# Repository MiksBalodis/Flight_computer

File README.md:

# Aktīvās kontroles raķetes avionikas sistēma

## Projekta apraksts
Šis projekts paredz aktīvās kontroles raķetes avionikas sistēmas izstrādi, kas ietver gan raķetē iebūvētu avionikas datoru, gan zemes bāzi datu saņemšanai, uzglabāšanai un analīzei. Sistēma nodrošina aktīvu trajektorijas korekciju reāllaikā, izmantojot sensoru datus, vadības algoritmus un elektroniskos izpildmehānismus.

Projektā tiek apvienotas iegultās sistēmas, signālu apstrāde, vadības algoritmi, telemetrija un lietotāja saskarnes izstrāde.

**Projektu izstrādā:**  
Aleksandrs Jesiļevskis  
Miks Balodis  

---

## Projekta mērķis
Izstrādāt:
- raķetes avionikas datoru ar aktīvas trajektorijas korekcijas iespējām,
- zemes bāzi lidojuma datu saņemšanai un analīzei,
- drošu un papildināmu sistēmu, kas piemērota eksperimentālām lieljaudas raķetēm.

Sistēmai jāspēj:
- reāllaikā noteikt raķetes stāvokli,
- veikt aktīvo vadību ar vairākām kontroles spurām,
- ierakstīt un uzglabāt lidojuma datus,
- nodrošināt saziņu ar zemes bāzi lidojuma laikā.

---

## Idejas rašanās
Ideja radās, balstoties uz **RTU Lieljaudas raķeškomandas (RTU HPR)** 2025. gada 1. semestra projektu – aktīvās rotācijas kontroles raķeti. Šī projekta ietvaros tika izmantots RP2040 mikrokontrolieris, kuram konstatēti vairāki ierobežojumi:
- nav iebūvēta peldošā komata vienības (FPU),
- ierobežota programmas atmiņa,
- augsts enerģijas patēriņš.

Lai šos trūkumus novērstu, projektā tiek izvēlēts **STM32F405RGT6**, kas nodrošina augstāku veiktspēju, FPU atbalstu un DSP instrukcijas.

---

## Idejas apraksts

### Projekta lietotāji
- studentu raķešu komandas,
- augstskolu/vidusskolu eksperimentēšanas grupas,
- iegulto sistēmu un vadības algoritmu izstrādātāji,
- eksperimentālu raķešu un bezpilota sistēmu entuziasti.

### Izmantotās tehnoloģijas
- **Iegultās sistēmas:** STM32 (ARM Cortex-M4)
- **Sensori:** barometrs, IMU, GNSS
- **Vadības algoritmi:** PID, Kalmana filtrs
- **Telemetrija:** sub-GHz radio sakari
- **Programmatūra:** C/C++, MatLab/Simulink (simulācijas), JavaScript un Svelte (GUI)
- **Projektēšana:** KiCad

### Piegādes formāts
Projekta rezultāts būs:
- raķetes avionikas sistēmas plate (PCB),
- iegultā programmatūra gatava demonstratīvam raķetes lidojumam (firmware),
- zemes bāzes programmatūra (GUI),
- dokumentācija.

Šāda pieeja ļauj sistēmu izmantot gan eksperimentālos lidojumos, gan simulācijās.

---

## Aktīvā kontrole
Aktīvā kontrole ir vadības sistēma, kas lidojuma laikā nepārtraukti:
- mēra raķetes stāvokli (leņķi, ātrumu, rotāciju),
- aprēķina nepieciešamos labojumus,
- ģenerē PWM signālus izpildmehānismiem servo kontrolētām spurām.

Sistēma atbalsta līdz **4 aktīvām spurām**, katrai paredzot atsevišķu PWM kanālu. Salīdzinājumā ar pasīvo kontroli, aktīvā kontrole spēj reaģēt uz ārējiem traucējumiem un uzlabot stabilitāti un precizitāti.

---

## Risinājuma arhitektūra

### Konceptuālais modelis
Sistēma sastāv no trim galvenajiem blokiem:
1. **Sensoru slānis** – datu iegūšana
2. **Vadības un apstrādes slānis** – aprēķini un lēmumu pieņemšana
3. **Izpildes un komunikācijas slānis** – kontrole, datu uzglabāšana un pārraide

### Tehniskā arhitektūra

#### MCU
- **STM32F405RGT6** - mikrokontrolieris datu apstrādei un komandu nodošanai

#### Sensori
- **BMP388** – barometrs augstuma noteikšanai
- **LSM6DSO** – IMU (akselerometrs + žiroskops)
- **MAX-M10S** – GNSS modulis augstas precizitātes pozīcijai

#### Datu uzglabāšana
- **MXL1606** – lidojuma datu ierakstīšanai (USB Mass Storage režīms)
- **24LC64 EEPROM** – konfigurācijas datiem

#### Telemetrija
- **EBYTE E22-400M22S** - LoRa moudlis saziņai ar zemes bāzi (433 MHz)

#### Vadība
- PWM signāli spuru servo
- PID regulators
- Kalmana filtrs stāvokļa novērtēšanai

---
## Izstrādes plāns (10 nedēļas)

Projekta izstrāde ir plānota 10 nedēļu laikā, pieņemot, ka avionikas plate jau ir uzdizainēta un pasūtīta, un nākamais solis ir tās salodēšana. Darbs tiek sadalīts starp diviem izstrādātājiem, lai maksimāli efektīvi izmantotu paralēlu izstrādi.

### Lomu sadalījums
- **Aleksandrs** – iegultās sistēmas programmēšana, STM32 firmware, sensoru draiveri, datu plūsma, vadība un telemetrija, sistēmas arhitektūras lēmumi,  integrācija, testēšana un dokumentācija.
- **Miks** – raķetes tehniskā daļa, mehāniskā integrācija, Matlab/Simulink simulācijas, vadības algoritmu modelēšana un zemes stacijas aparatūra, sistēmas arhitektūras lēmumi,  integrācija, testēšana un dokumentācija.

---

### 1. nedēļa – Sistēmas inicializācija un modeļu sagatavošana
**Aleksandrs:**
- STM32CubeIDE projekta izveide
- Pulksteņu (clock tree) un pamata perifēriju konfigurācija
- Debug interfeisa (SWD/UART) inicializācija

**Miks:**
- Raķetes kustības konceptuālā modeļa izstrāde
- Aktīvās kontroles uzdevuma definēšana
- Sensoru mērījumu teorētisko modeļu izveide

**Rezultāts:**  
MCU veiksmīgi startē un sistēmas matemātiskais modelis ir definēts.

---

### 2. nedēļa – Perifēriju un datu plūsmas pamati
**Aleksandrs:**
- GPIO, UART, SPI un I2C konfigurācija
- DMA izmantošanas pamati datu pārsūtīšanai
- Vienkārša datu izvada testēšana

**Miks:**
- PID regulatora struktūras izveide Matlab/Simulink
- Sākotnējo vadības parametru novērtēšana
- Avionikas plates salodēšana

**Rezultāts:**  
MCU spēj komunicēt ar perifērijām, un PID struktūra ir gatava simulācijām, plate ir salodēta.

---

### 3. nedēļa – Avionikas plates salodēšana un sensoru testēšana
**Aleksandrs:**
- IMU (LSM6DSO) un barometra (BMP388) draiveru izstrāde
- Sensoru datu nolasīšana un izvadīšana caur UART

**Miks:**
- Barošanas un signālu līmeņu pārbaude
- Sensoru fiziskās integrācijas novērtēšana

**Rezultāts:**  
Pilnībā funkcionējoši aktīvie sensori.

---

### 4. nedēļa – GNSS un sensoru apvienošana
**Aleksandrs:**
- GNSS (MAX-M10S) draivera izstrāde
- Laika sinhronizācija starp sensoriem
- Datu struktūru definēšana

**Miks:**
- Sensoru kalibrācijas metodes
- Kļūdu modelēšana
- Mērījumu precizitātes izvērtēšana

**Rezultāts:**  
Apvienoti visi sensoru dati vienotā laika skalā.

---

### 5. nedēļa – Aktīvā vadība un izpildmehānismi
**Aleksandrs:**
- PWM izvades konfigurācija
- Taimeru konfigurācija izpildmehānismiem
- Izpildmehānismu testēšana

**Miks:**
- PID parametru regulēšana Simulink vidē
- Stabilitātes analīze
- Vadības algoritma validācija simulācijā

**Rezultāts:**  
Izpildmehānismi reaģē uz vadības signāliem paredzētajā veidā.

---

### 6. nedēļa – Datu apstrāde un uzglabāšana
**Aleksandrs:**
- USB Mass Storage režīma ieviešana
- Datu struktūras optimizācija

**Miks:**
- Kalmana filtra izstrāde Simulink vidē
- Algoritma sagatavošana ieviešanai C kodā

**Rezultāts:**  
Stabili ierakstīti un izgūstami lidojuma dati.

---

### 7. nedēļa – Telemetrija un zemes stacijas aparatūra
**Aleksandrs:**
- Telemetrijas protokola izstrāde
- EBYTE E22 radio moduļa integrācija
- Datu pakešu formāta definēšana

**Miks:**
- Zemes stacijas plates arhitektūras izstrāde
- Komponentu izvēle un shēmas dizains
- Komunikācijas interfeisa plānošana

**Rezultāts:**  
Bezvadu datu pārraide starp raķeti un zemes staciju.

---

### 8. nedēļa – Zemes stacijas programmatūra un GUI
**Aleksandrs:**
- Seriālās komunikācijas protokols ar datoru
- Telemetrijas datu parsēšana

**Miks:**
- Grafiskās lietotāja saskarnes izstrāde (Svelte)
- Reāllaika grafiki un datu attēlošana
- Datu eksportēšana analīzei

**Rezultāts:**  
Darbojoša zemes stacija ar reāllaika datu vizualizāciju.

---

### 9. nedēļa – Integrācija un sistēmas testi
**Aleksandrs:**
- Pilna vadības cikla integrācija
- Kļūdu apstrāde un drošības mehānismi

**Miks:**
- Vibrāciju testi
- Sensoru trokšņu ietekmes pārbaude

**Rezultāts:**  
Stabila un integrēta sistēma bez kritiskām kļūdām.

---

### 10. nedēļa – Stabilizācija un dokumentācija
**Abi:**
- Koda un aparatūras kļūdu labošana
- Projekta dokumentācijas pabeigšana
- Demonstrācijas sagatavošana

**Rezultāts:**  
Pilnībā sagatavots projekts demonstrācijai un prezentācijai.

---

## Projekta izstrādes grafiks

---

## Licence
Licence tiks noteikta projekta vēlākā izstrādes posmā.

---

## Kontakti
Jautājumu vai sadarbības gadījumā sazināties ar projekta izstrādātājiem.

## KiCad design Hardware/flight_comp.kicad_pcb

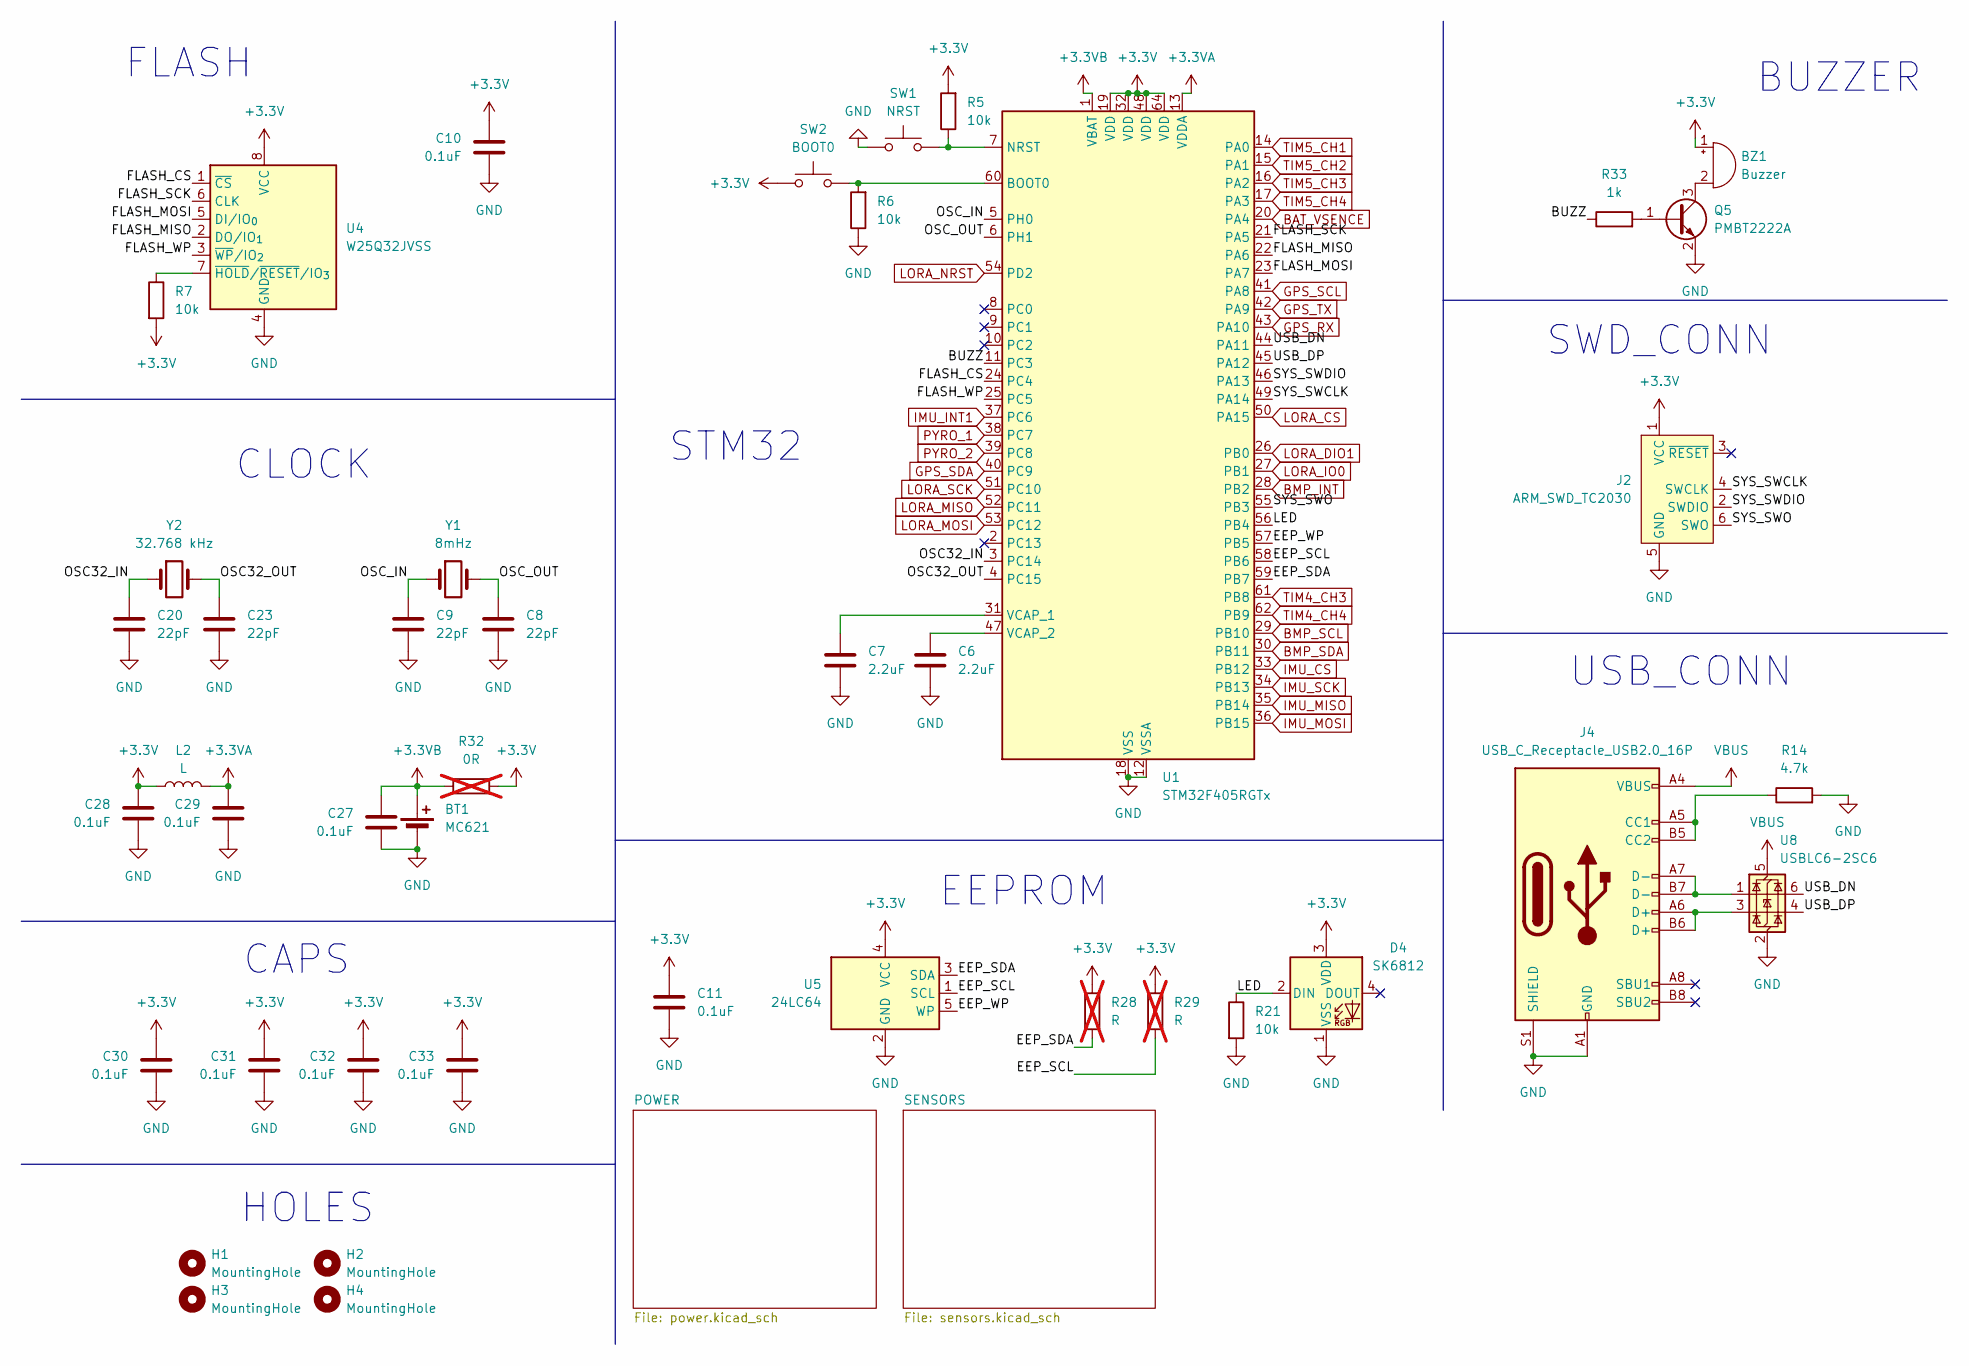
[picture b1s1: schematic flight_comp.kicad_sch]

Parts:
BT1: MC621; BatteryHolder_Keystone_2998_1x6.8mm
BZ1: Buzzer; Buzzer_CUI_CPT-9019S-SMT
C6, C7: 2.2uF; C_0603_1608Metric
C8, C9, C20, C23: 22pF; C_0603_1608Metric
C10, C11, C27, C28, C29, C30, C31, C32, C33: 0.1uF; C_0603_1608Metric
D4: SK6812; LED_SK6812_PLCC4_5.0x5.0mm_P3.2mm
H1, H2, H3, H4: MountingHole; MountingHole_3.2mm_M3
J2: ARM_SWD_TC2030; Tag-Connect_TC2030-IDC-NL_2x03_P1.27mm_Vertical
J4: USB_C_Receptacle_USB2.0_16P; USB_C_Receptacle_GCT_USB4110
L2: L; L_0603_1608Metric
Q5: PMBT2222A; SOT-23
R5, R6, R7, R21: 10k; R_0603_1608Metric
R14: 4.7k; R_0603_1608Metric
R28, R29: R; R_0603_1608Metric; not fitted
R32: 0R; R_0603_1608Metric; not fitted
R33: 1k; R_0603_1608Metric
SW1: NRST; SW_SPST_CK_RS282G05A3
SW2: BOOT0; SW_SPST_CK_RS282G05A3
U1: STM32F405RGTx; LQFP-64_10x10mm_P0.5mm
U4: W25Q32JVSS; SOIC-8_5.3x5.3mm_P1.27mm
U5: 24LC64; SOT-23-5
U8: USBLC6-2SC6; SOT-23-6
Y1: 8mHz; Crystal_SMD_5032-2Pin_5.0x3.2mm
Y2: 32.768 kHz; Crystal_SMD_3215-2Pin_3.2x1.5mm

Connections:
+3.3VA: C29.1, L2.2, U1.13 (VDDA)
+3.3VB: BT1.1 (+), C27.1, R32.1, U1.1 (VBAT)
BAT_VSENCE: U1.20 (PA4); also elsewhere on the board
BMP_INT: U1.28 (PB2); also elsewhere on the board
BMP_SCL: U1.29 (PB10); also elsewhere on the board
BMP_SDA: U1.30 (PB11); also elsewhere on the board
BUZZ: R33.1, U1.11 (PC3)
CAMERA_SWITCH: U1.8 (PC0); also elsewhere on the board
EEP_SCL: R29.2, U1.58 (PB6), U5.1 (SCL)
EEP_SDA: R28.2, U1.59 (PB7), U5.3 (SDA)
EEP_WP: U1.57 (PB5), U5.5 (WP)
FLASH_CS: U1.24 (PC4), U4.1 (~CS)
FLASH_MISO: U1.22 (PA6), U4.2 (DO/IO_{1})
FLASH_MOSI: U1.23 (PA7), U4.5 (DI/IO_{0})
FLASH_SCK: U1.21 (PA5), U4.6 (CLK)
FLASH_WP: U1.25 (PC5), U4.3 (~WP/IO_{2})
GPS_RX: U1.43 (PA10); also elsewhere on the board
GPS_SCL: U1.41 (PA8); also elsewhere on the board
GPS_SDA: U1.40 (PC9); also elsewhere on the board
GPS_TX: U1.42 (PA9); also elsewhere on the board
IMU_CS: U1.33 (PB12); also elsewhere on the board
IMU_INT1: U1.37 (PC6); also elsewhere on the board
IMU_MISO: U1.35 (PB14); also elsewhere on the board
IMU_MOSI: U1.36 (PB15); also elsewhere on the board
IMU_SCK: U1.34 (PB13); also elsewhere on the board
LED: D4.2 (DIN), R21.1, U1.56 (PB4)
LORA_CS: U1.50 (PA15); also elsewhere on the board
LORA_DIO1: U1.26 (PB0); also elsewhere on the board
LORA_IO0: U1.27 (PB1); also elsewhere on the board
LORA_MISO: U1.52 (PC11); also elsewhere on the board
LORA_MOSI: U1.53 (PC12); also elsewhere on the board
LORA_NRST: U1.54 (PD2); also elsewhere on the board
LORA_SCK: U1.51 (PC10); also elsewhere on the board
unnamed: BZ1.2 (-), Q5.3 (C)
unnamed: J4.A5 (CC1), J4.B5 (CC2), R14.1
unnamed: J4.A6 (D+), J4.B6 (D+), U8.3 (I/O2)
unnamed: J4.A7 (D-), J4.B7 (D-), U8.1 (I/O1)
unnamed: Q5.1 (B), R33.2
unnamed: R6.2, SW2.2, U1.60 (BOOT0)
unnamed: R5.1, SW1.2, U1.7 (NRST)
unnamed: C7.1, U1.31 (VCAP_1)
unnamed: C6.1, U1.47 (VCAP_2)
unnamed: R7.1, U4.7 (~HOLD/~RESET/IO_{3})
OSC32_IN: C20.1, U1.3 (PC14), Y2.1
OSC32_OUT: C23.1, U1.4 (PC15), Y2.2
OSC_IN: C9.1, U1.5 (PH0), Y1.1
OSC_OUT: C8.1, U1.6 (PH1), Y1.2
PYRO_1: U1.38 (PC7); also elsewhere on the board
PYRO_2: U1.39 (PC8); also elsewhere on the board
SYS_SWCLK: J2.4 (SWCLK), U1.49 (PA14)
TIM4_CH3: U1.61 (PB8); also elsewhere on the board
TIM4_CH4: U1.62 (PB9); also elsewhere on the board
TIM5_CH1: U1.14 (PA0); also elsewhere on the board
TIM5_CH2: U1.15 (PA1); also elsewhere on the board
TIM5_CH3: U1.16 (PA2); also elsewhere on the board
TIM5_CH4: U1.17 (PA3); also elsewhere on the board
USB_DN: U1.44 (PA11), U8.6 (I/O1)
USB_DP: U1.45 (PA12), U8.4 (I/O2)
VBUS: J4.A4 (VBUS), J4.A9 (VBUS), J4.B4 (VBUS), J4.B9 (VBUS), U8.5 (VBUS); also elsewhere on the board

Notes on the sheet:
CAPS
CLOCK
BUZZER
USB_CONN
EEPROM
STM32
SWD_CONN
HOLES
FLASH

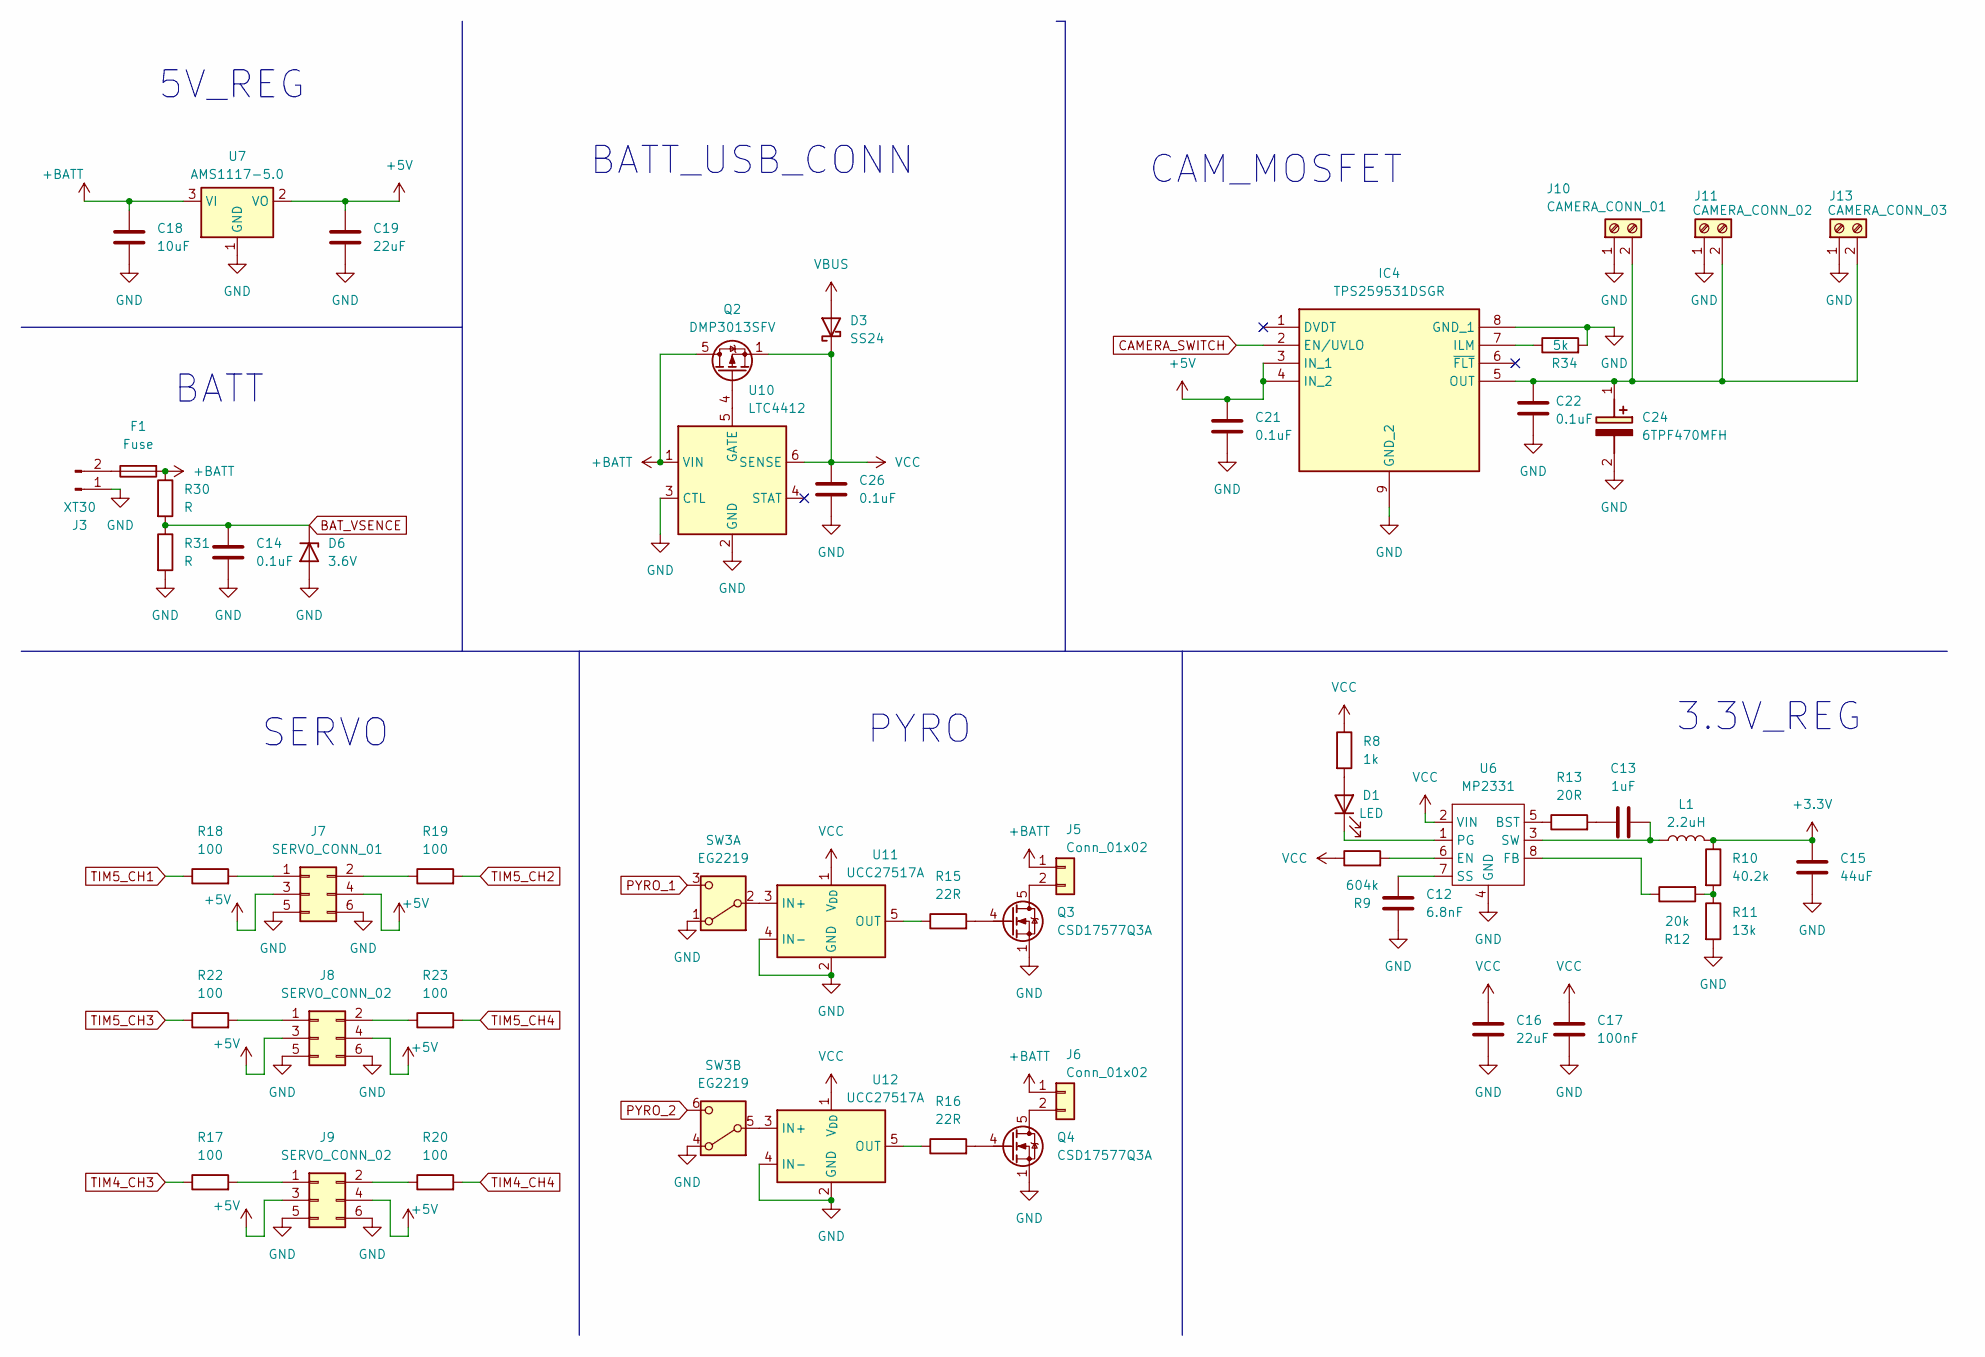
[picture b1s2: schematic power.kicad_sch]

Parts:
C12: 6.8nF; C_0603_1608Metric
C13: 1uF; C_0603_1608Metric
C14, C26: 0.1uF; C_0603_1608Metric
C15: 44uF; C_0805_2012Metric
C16: 22uF; C_0805_2012Metric
C17: 100nF; C_0603_1608Metric
C18: 10uF; C_0603_1608Metric
C19: 22uF; C_0603_1608Metric
C21, C22: 0.1uF; C_0402_1005Metric; MPN C0402C104K4RAC7411
C24: 6TPF470MFH; CP_EIA-3216-10_Kemet-I; Mouser Part Number 667-6TPF470MFH
D1: LED; LED_0603_1608Metric
D3: SS24; D_SMA
D6: 3.6V; D_SOD-128
F1: Fuse; Fuse_1206_3216Metric
IC4: TPS259531DSGR; WSON-8-1EP_2x2mm_P0.5mm_EP0.9x1.6mm_ThermalVias; Mouser Part Number 595-TPS259531DSGR
J3: XT30; AMASS_XT30PW-M_1x02_P2.50mm_Horizontal
J5, J6: Conn_01x02; TerminalBlock_4Ucon_1x02_P3.50mm_Vertical; MPN 284514-2
J7: SERVO_CONN_01; PinHeader_2x03_P2.54mm_Vertical; MPN 90131-0763
J8, J9: SERVO_CONN_02; PinHeader_2x03_P2.54mm_Vertical; MPN 90131-0763
J10: CAMERA_CONN_01; TerminalBlock_Xinya_XY308-2.54-2P_1x02_P2.54mm_Horizontal; MPN 284514-2
J11: CAMERA_CONN_02; TerminalBlock_Xinya_XY308-2.54-2P_1x02_P2.54mm_Horizontal; MPN 284514-2
J13: CAMERA_CONN_03; TerminalBlock_Xinya_XY308-2.54-2P_1x02_P2.54mm_Horizontal; MPN 284514-2
L1: 2.2uH; L_6.3x6.3_H3
Q2: DMP3013SFV; Diodes_PowerDI3333-8
Q3, Q4: CSD17577Q3A; VSON-8_3.3x3.3mm_P0.65mm_NexFET
R8: 1k; R_0603_1608Metric
R9: 604k; R_0603_1608Metric
R10: 40.2k; R_0603_1608Metric
R11: 13k; R_0603_1608Metric
R12: 20k; R_0603_1608Metric
R13: 20R; R_0603_1608Metric
R15, R16: 22R; R_0603_1608Metric
R17, R19, R20, R22, R23: 100; R_0402_1005Metric; MPN RC1206FR-07100RL
R18: 100; R_0402_1005Metric
R30, R31: R; R_0603_1608Metric
R34: 5k; R_0402_1005Metric; MPN RC0402FR-075K76L
SW3: EG2219; SW_DPDT_CK_JS202011JCQN
U6: MP2331; SOT-583-8
U7: AMS1117-5.0; SOT-223-3_TabPin2
U10: LTC4412; TSOT-23-6
U11, U12: UCC27517A; SOT-23-5

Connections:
+BATT: C18.1, F1.2, J5.1, J6.1, Q2.5 (D), R30.1, U7.3 (VI), U10.1 (VIN); also elsewhere on the board
BAT_VSENCE: C14.1, D6.1 (K), R30.2, R31.1; also elsewhere on the board
CAMERA_SWITCH: IC4.2 (EN/UVLO); also elsewhere on the board
unnamed: C13.1, R13.2
unnamed: C22.1, C24.1 (+), IC4.5 (OUT), J10.2, J11.2, J13.2
unnamed: D1.2 (A), R8.2
unnamed: D1.1 (K), U6.1 (PG)
unnamed: IC4.7 (ILM), R34.1
unnamed: F1.1, J3.2
unnamed: J5.2, Q3.5 (D)
unnamed: J6.2, Q4.5 (D)
unnamed: J7.1, R18.2
unnamed: J7.2, R19.1
unnamed: J8.1, R22.2
unnamed: J8.2, R23.1
unnamed: J9.1, R17.2
unnamed: J9.2, R20.1
unnamed: Q2.4 (G), U10.5 (GATE)
unnamed: Q3.4 (G), R15.2
unnamed: Q4.4 (G), R16.2
unnamed: R10.2, R11.1, R12.2
unnamed: SW3.2 (B), U11.3 (IN+)
unnamed: SW3.5 (B), U12.3 (IN+)
unnamed: R13.1, U6.5 (BST)
unnamed: R9.2, U6.6 (EN)
unnamed: R12.1, U6.8 (FB)
unnamed: C12.1, U6.7 (SS)
unnamed: C13.2, L1.1, U6.3 (SW)
unnamed: R15.1, U11.5 (OUT)
unnamed: R16.1, U12.5 (OUT)
PYRO_1: SW3.3 (C); also elsewhere on the board
PYRO_2: SW3.6 (C); also elsewhere on the board
TIM4_CH3: R17.1; also elsewhere on the board
TIM4_CH4: R20.2; also elsewhere on the board
TIM5_CH1: R18.1; also elsewhere on the board
TIM5_CH2: R19.2; also elsewhere on the board
TIM5_CH3: R22.1; also elsewhere on the board
TIM5_CH4: R23.2; also elsewhere on the board
VBUS: D3.2 (A); also elsewhere on the board
VCC: C16.1, C17.1, C26.1, D3.1 (K), Q2.1 (S), Q2.2 (S), Q2.3 (S), R8.1, R9.1, U6.2 (VIN), U10.6 (SENSE), U11.1 (V_{DD}), U12.1 (V_{DD})

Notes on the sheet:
SERVO
PYRO
BATT_USB_CONN
5V_REG
3.3V_REG
BATT
CAM_MOSFET

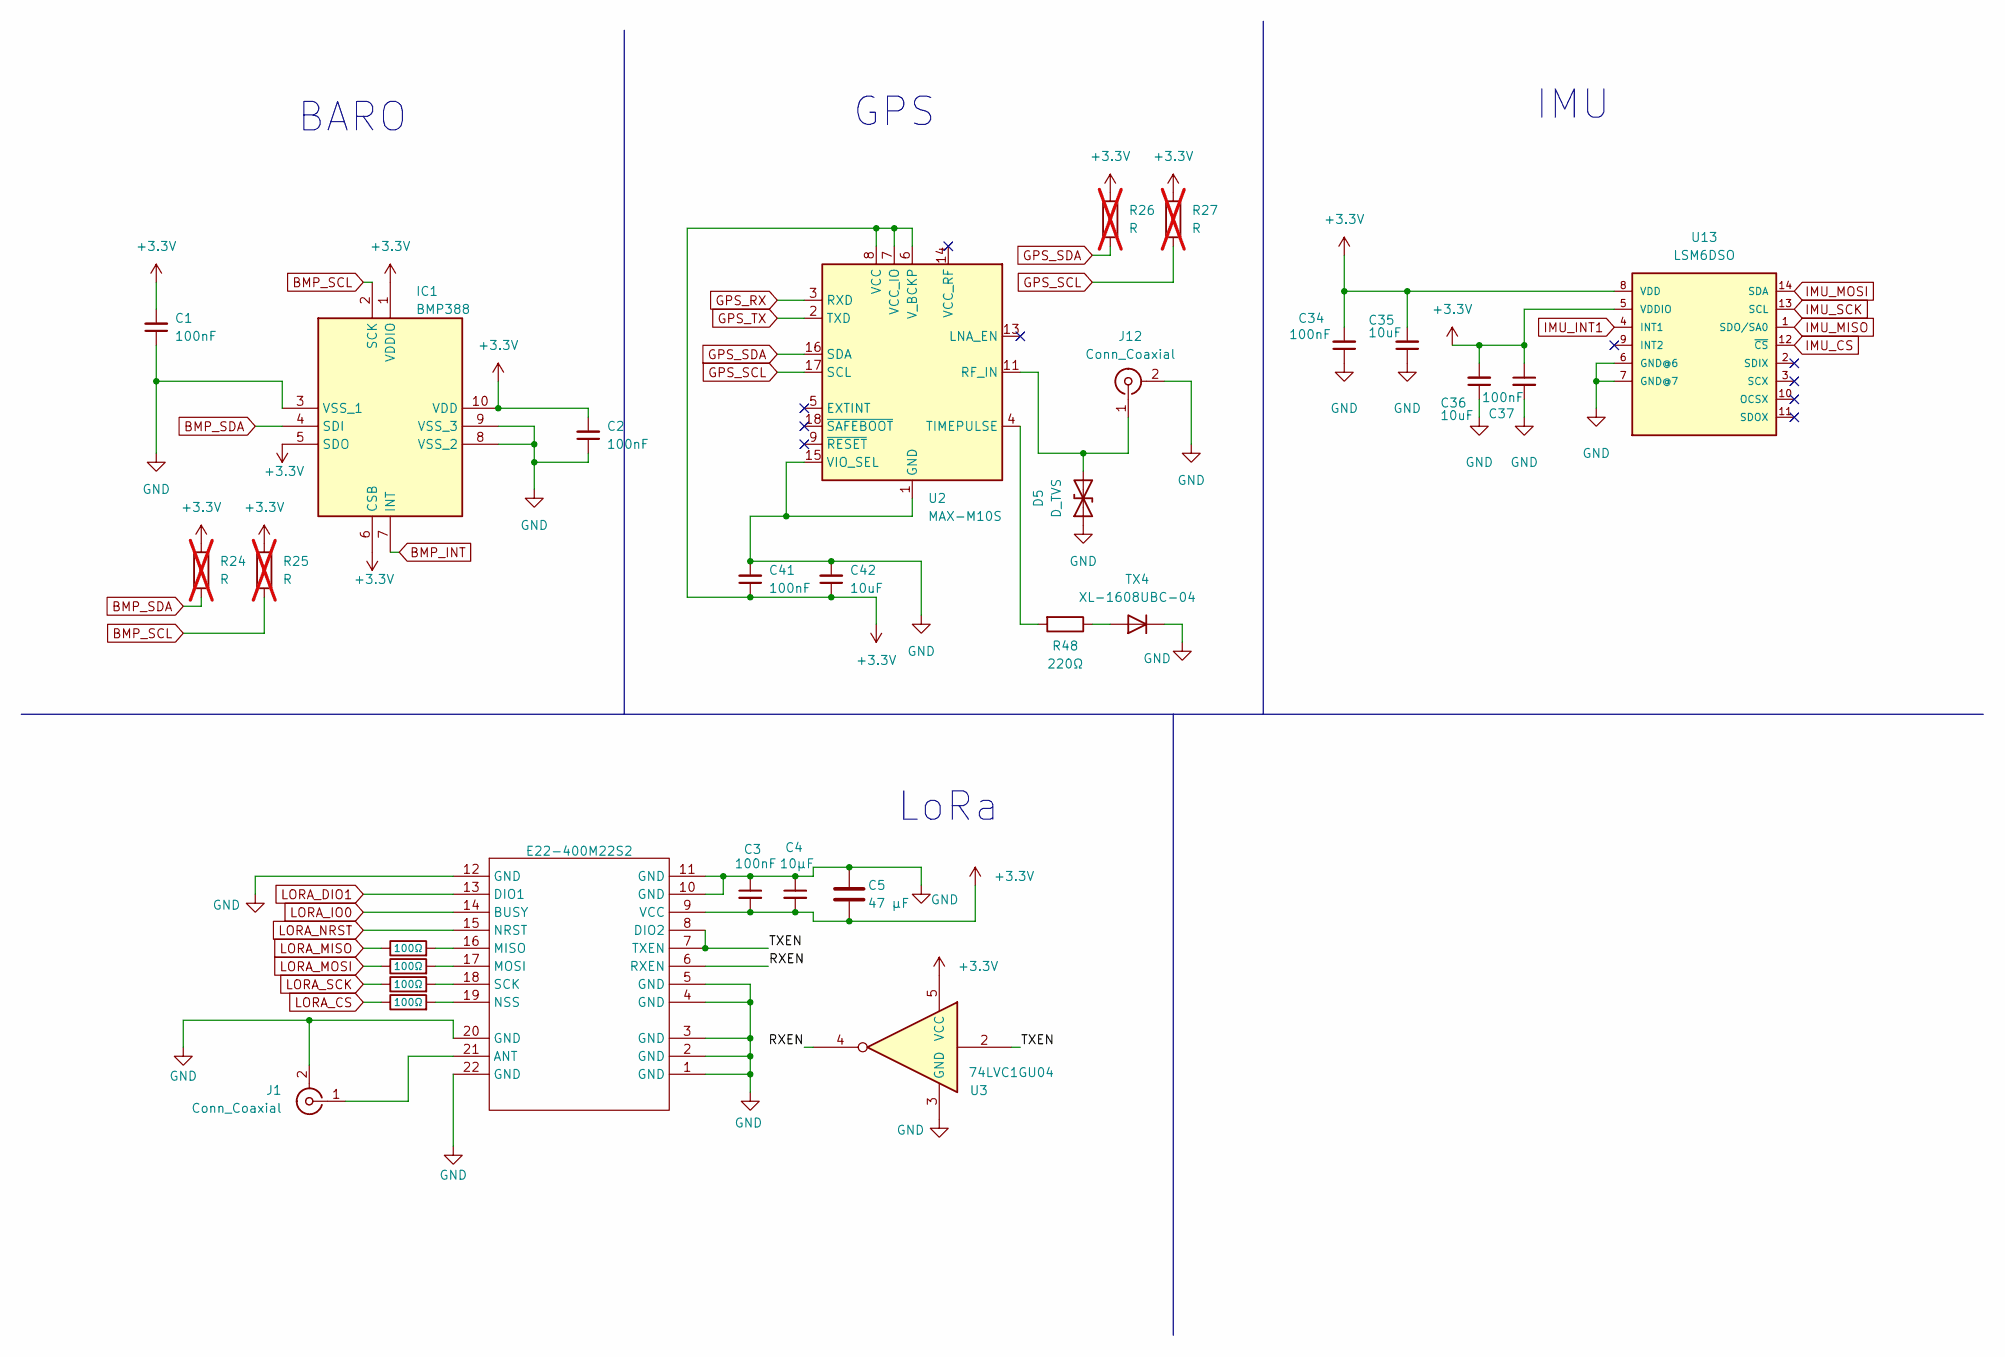
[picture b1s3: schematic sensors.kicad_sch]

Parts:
C1, C2, C3, C41: 100nF; C_0402_1005Metric
C4: 10µF; C_0402_1005Metric
C5: 47 µF; C_1206_3216Metric
C34, C37: 100nF; C_0402_1005Metric; MPN C0402C104K4RAC7411
C35, C36: 10uF; C_0402_1005Metric; MPN C0402C106M9PACTU
C42: 10uF; C_0603_1608Metric
D5: D_TVS; D_SOD-523
E22-400M22S2: E22-400M22S
IC1: BMP388; ST_HLGA-10_2x2mm_P0.5mm_LayoutBorder3x2y; Manufacturer_Part_Number BMP388
J1, J12: Conn_Coaxial; SMA_Molex_73251-2200_Horizontal
R1, R2, R3, R4: 100Ω; R_0402_1005Metric
R24, R25, R26, R27: R; R_0603_1608Metric; not fitted
R48: 220Ω; R_0402_1005Metric
TX4: XL-1608UBC-04; LED_0603_1608Metric
U2: MAX-M10S; ublox_MAX
U3: 74LVC1GU04; SOT-23-5
U13: LSM6DSO; LGA-14_3x2.5mm_P0.5mm_LayoutBorder3x4y; MPN LSM6DSOTR

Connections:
/SENSORS/RXEN: E22-400M22S2.6 (RXEN), U3.4
/SENSORS/TXEN: E22-400M22S2.7 (TXEN), E22-400M22S2.8 (DIO2), U3.2
BMP_INT: IC1.7 (INT); also elsewhere on the board
BMP_SCL: IC1.2 (SCK), R25.2; also elsewhere on the board
BMP_SDA: IC1.4 (SDI), R24.2; also elsewhere on the board
GPS_RX: U2.3 (RXD); also elsewhere on the board
GPS_SCL: R27.2, U2.17 (SCL); also elsewhere on the board
GPS_SDA: R26.2, U2.16 (SDA); also elsewhere on the board
GPS_TX: U2.2 (TXD); also elsewhere on the board
IMU_CS: U13.12 (~CS); also elsewhere on the board
IMU_INT1: U13.4 (INT1); also elsewhere on the board
IMU_MISO: U13.1 (SDO/SA0); also elsewhere on the board
IMU_MOSI: U13.14 (SDA); also elsewhere on the board
IMU_SCK: U13.13 (SCL); also elsewhere on the board
LORA_CS: R4.1; also elsewhere on the board
LORA_DIO1: E22-400M22S2.13 (DIO1); also elsewhere on the board
LORA_IO0: E22-400M22S2.14 (BUSY); also elsewhere on the board
LORA_MISO: R1.1; also elsewhere on the board
LORA_MOSI: R2.1; also elsewhere on the board
LORA_NRST: E22-400M22S2.15 (NRST); also elsewhere on the board
LORA_SCK: R3.1; also elsewhere on the board
unnamed 41: E22-400M22S2.21 (ANT), J1.1 (In); also elsewhere on the board
unnamed: D5.2 (A2), J12.1 (In), U2.11 (RF_IN)
unnamed: E22-400M22S2.16 (MISO), R1.2
unnamed: E22-400M22S2.17 (MOSI), R2.2
unnamed: E22-400M22S2.19 (NSS), R4.2
unnamed: E22-400M22S2.18 (SCK), R3.2
unnamed: R48.1, TX4.2 (A)
unnamed: R48.2, U2.4 (TIMEPULSE)

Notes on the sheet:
GPS
IMU
LoRa
BARO

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
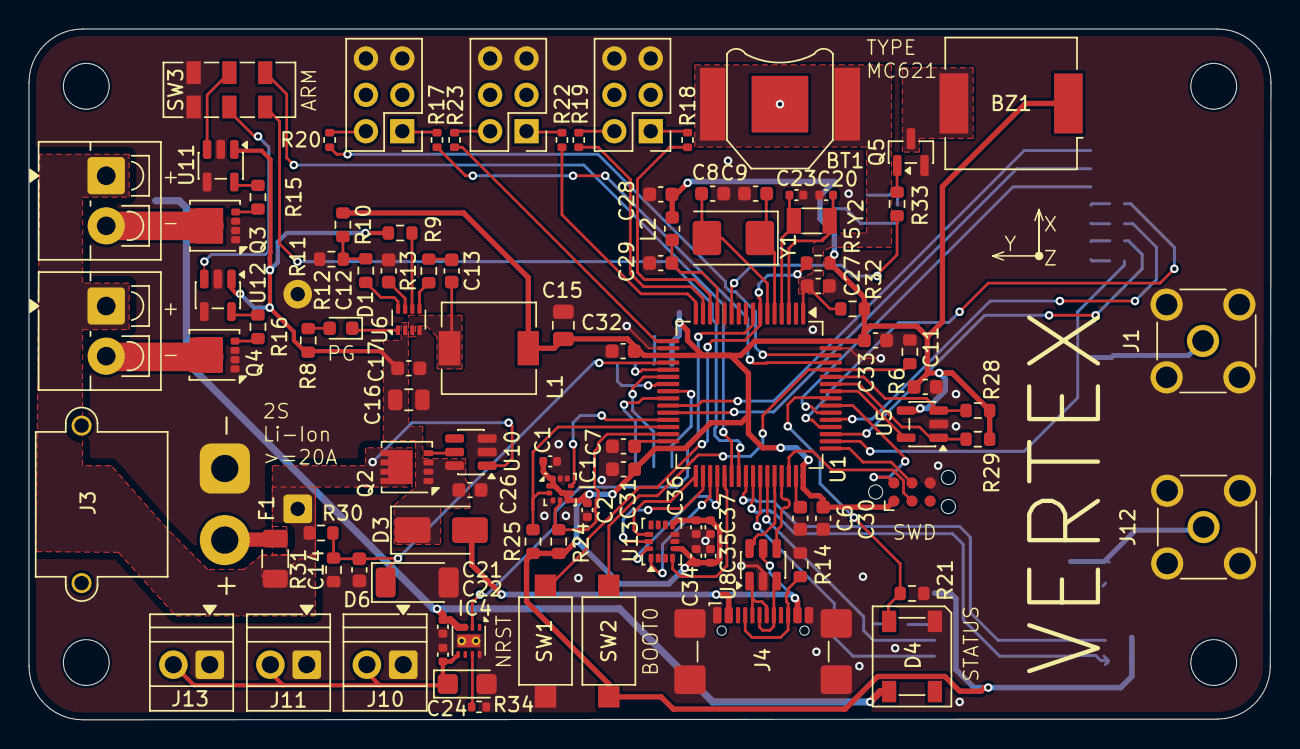
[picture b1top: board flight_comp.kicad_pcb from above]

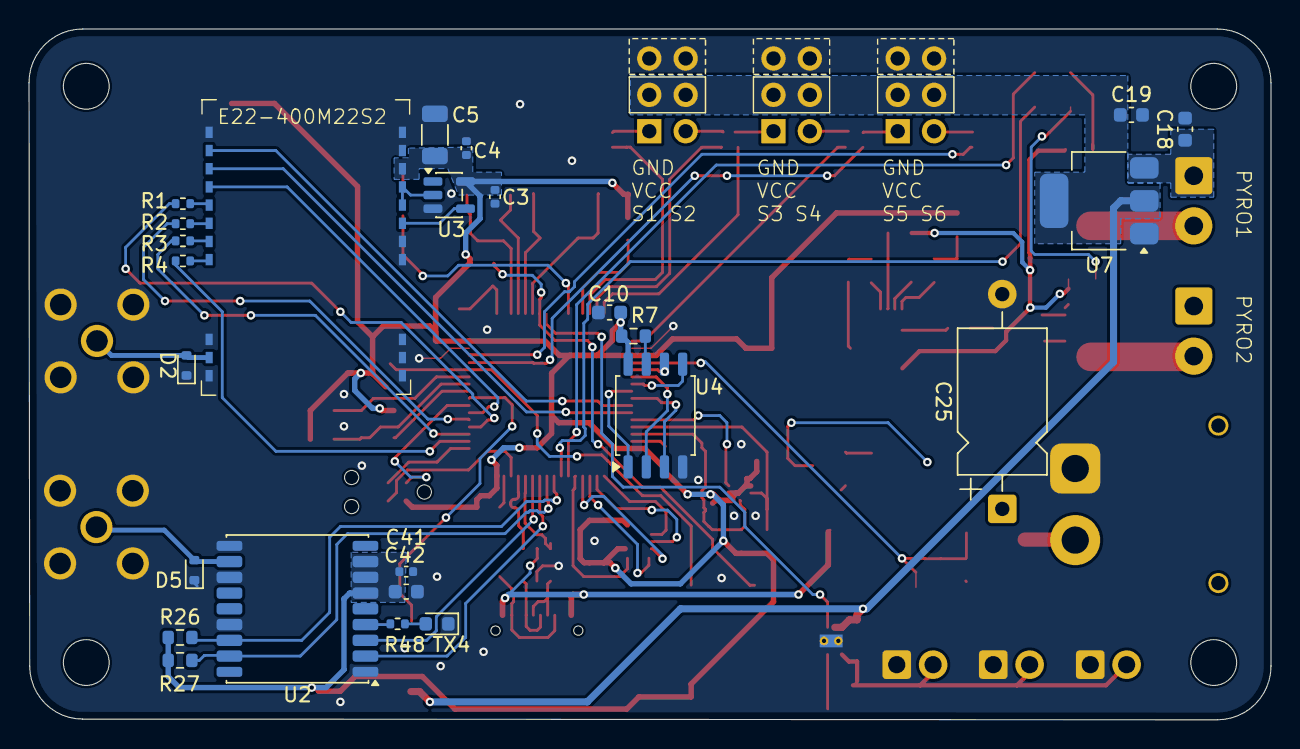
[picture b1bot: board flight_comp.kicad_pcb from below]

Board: 4 copper layers, 86.7 x 48.2 mm, 127 parts (25 on the bottom side), 103 nets.

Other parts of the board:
C25: 1000uF; CP_Axial_L10.0mm_D6.0mm_P15.00mm_Horizontal
D2: D_TVS; D_SOD-523

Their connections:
+BATT: C25.1; also elsewhere on the board
unnamed 41: D2.2 (A2); also elsewhere on the board

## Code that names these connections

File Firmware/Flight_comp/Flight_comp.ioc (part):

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Mcu.Name=STM32F405RGTx
Mcu.Package=LQFP64
Mcu.UserName=STM32F405RGTx
PA0-WKUP.GPIOParameters=GPIO_Label
PA0-WKUP.GPIO_Label=SERVO1
PA0-WKUP.Signal=S_TIM5_CH1
PA1.GPIOParameters=GPIO_Label
PA1.GPIO_Label=SERVO2
PA1.Signal=S_TIM5_CH2
PA10.GPIOParameters=GPIO_Label
PA10.GPIO_Label=GPS_RX
PA10.Mode=Asynchronous
PA10.Signal=USART1_RX
PA11.Mode=Device_Only
PA11.Signal=USB_OTG_FS_DM
PA12.Mode=Device_Only
PA12.Signal=USB_OTG_FS_DP
PA13.Mode=Trace_Asynchronous_SW
PA13.Signal=SYS_JTMS-SWDIO
PA14.Mode=Trace_Asynchronous_SW
PA14.Signal=SYS_JTCK-SWCLK
PA15.GPIOParameters=GPIO_Label
PA15.GPIO_Label=LORA_NSS
PA15.Mode=NSS_Signal_Hard_Output
PA15.Signal=SPI3_NSS
PA2.GPIOParameters=GPIO_Label
PA2.GPIO_Label=SERVO3
PA2.Signal=S_TIM5_CH3
PA3.GPIOParameters=GPIO_Label
PA3.GPIO_Label=SERVO4
PA3.Signal=S_TIM5_CH4
PA4.GPIOParameters=GPIO_Label
PA4.GPIO_Label=BAT_VSENCE
PA4.Signal=ADCx_IN4
PA5.GPIOParameters=GPIO_Label
PA5.GPIO_Label=FLASH_SCK
PA5.Mode=Full_Duplex_Master
PA5.Signal=SPI1_SCK
PA6.GPIOParameters=GPIO_Label
PA6.GPIO_Label=FLASH_MISO
PA6.Mode=Full_Duplex_Master
PA6.Signal=SPI1_MISO
PA7.GPIOParameters=GPIO_Label
PA7.GPIO_Label=FLASH_MOSI
PA7.Mode=Full_Duplex_Master
PA7.Signal=SPI1_MOSI
PA8.GPIOParameters=GPIO_Label,GPIO_Pu
PA8.GPIO_Label=GPS_SCL
PA8.GPIO_Pu=GPIO_PULLUP
PA8.Mode=I2C
PA8.Signal=I2C3_SCL
PA9.GPIOParameters=GPIO_Label
PA9.GPIO_Label=GPS_TX
PA9.Mode=Asynchronous
PA9.Signal=USART1_TX
PB0.GPIOParameters=GPIO_Label
PB0.GPIO_Label=LORA_DIO1
PB0.Signal=GPIO_Output
PB1.GPIOParameters=GPIO_Label
PB1.GPIO_Label=LORA_IO0
PB1.Signal=GPIO_Input
PB10.GPIOParameters=GPIO_Label,GPIO_Pu
PB10.GPIO_Label=BMP_SCL
PB10.GPIO_Pu=GPIO_PULLUP
PB10.Mode=I2C
PB10.Signal=I2C2_SCL
PB11.GPIOParameters=GPIO_Label,GPIO_Pu
PB11.GPIO_Label=BMP_SDA
PB11.GPIO_Pu=GPIO_PULLUP
PB11.Mode=I2C
PB11.Signal=I2C2_SDA
PB12.GPIOParameters=GPIO_Label
PB12.GPIO_Label=IMU_NSS
PB12.Mode=NSS_Signal_Hard_Output
PB12.Signal=SPI2_NSS
PB13.GPIOParameters=GPIO_Label
PB13.GPIO_Label=IMU_SCK
PB13.Mode=Full_Duplex_Master
PB13.Signal=SPI2_SCK
PB14.GPIOParameters=GPIO_Label
PB14.GPIO_Label=IMU_MISO
PB14.Mode=Full_Duplex_Master
PB14.Signal=SPI2_MISO
PB15.GPIOParameters=GPIO_Label
PB15.GPIO_Label=IMU_MOSI
PB15.Mode=Full_Duplex_Master
PB15.Signal=SPI2_MOSI
PB2.GPIOParameters=GPIO_Label
PB2.GPIO_Label=BMP_INT
PB2.Signal=GPXTI2
PB3.Mode=Trace_Asynchronous_SW
PB3.Signal=SYS_JTDO-SWO
PB4.GPIOParameters=GPIO_Label
PB4.GPIO_Label=LED
PB4.Signal=S_TIM3_CH1
PB5.GPIOParameters=GPIO_Label
PB5.GPIO_Label=EEP_WP
PB5.Signal=GPIO_Output
PB6.GPIOParameters=GPIO_Label,GPIO_Pu
PB6.GPIO_Label=EEP_SCL
PB6.GPIO_Pu=GPIO_PULLUP
PB6.Mode=I2C
PB6.Signal=I2C1_SCL
PB7.GPIOParameters=GPIO_Label,GPIO_Pu
PB7.GPIO_Label=EEP_SDA
PB7.GPIO_Pu=GPIO_PULLUP
PB7.Mode=I2C
PB7.Signal=I2C1_SDA
PB8.GPIOParameters=GPIO_Label
PB8.GPIO_Label=SERVO5
PB8.Signal=S_TIM4_CH3
PB9.GPIOParameters=GPIO_Label
PB9.GPIO_Label=SERVO6
PB9.Signal=S_TIM4_CH4
PC0.GPIOParameters=GPIO_Label
PC0.GPIO_Label=CAM_CTRL
PC0.Signal=GPIO_Output
PC10.GPIOParameters=GPIO_Label
PC10.GPIO_Label=LORA_SCK
PC10.Mode=Full_Duplex_Master
PC10.Signal=SPI3_SCK
PC11.GPIOParameters=GPIO_Label
PC11.GPIO_Label=LORA-MISO
PC11.Mode=Full_Duplex_Master
PC11.Signal=SPI3_MISO
PC12.GPIOParameters=GPIO_Label
PC12.GPIO_Label=LORA_MOSI
PC12.Mode=Full_Duplex_Master
PC12.Signal=SPI3_MOSI
PC14-OSC32_IN.Mode=LSE-External-Oscillator
PC14-OSC32_IN.Signal=RCC_OSC32_IN
PC15-OSC32_OUT.Mode=LSE-External-Oscillator
PC15-OSC32_OUT.Signal=RCC_OSC32_OUT
PC3.GPIOParameters=GPIO_Label
PC3.GPIO_Label=BUZZER
PC3.Signal=GPIO_Output
PC4.GPIOParameters=GPIO_Speed,PinState,GPIO_Label
PC4.GPIO_Label=FLASH_NSS
PC4.GPIO_Speed=GPIO_SPEED_FREQ_VERY_HIGH
PC4.PinState=GPIO_PIN_SET
PC4.Signal=GPIO_Output
PC5.GPIOParameters=GPIO_Speed,PinState,GPIO_Label
PC5.GPIO_Label=FLASH_WP
PC5.GPIO_Speed=GPIO_SPEED_FREQ_VERY_HIGH
PC5.PinState=GPIO_PIN_SET
PC5.Signal=GPIO_Output
PC6.GPIOParameters=GPIO_Label
PC6.GPIO_Label=IMU_INT1
PC6.Signal=GPXTI6
PC7.GPIOParameters=GPIO_Label
PC7.GPIO_Label=PYRO1
PC7.Signal=GPIO_Output
PC8.GPIOParameters=GPIO_Label
PC8.GPIO_Label=PYRO2
PC8.Signal=GPIO_Output
PC9.GPIOParameters=GPIO_Label,GPIO_Pu
PC9.GPIO_Label=GPS_SDA
PC9.GPIO_Pu=GPIO_PULLUP
PC9.Mode=I2C
PC9.Signal=I2C3_SDA
PD2.GPIOParameters=GPIO_Label
PD2.GPIO_Label=LORA_NRST
PD2.Signal=GPIO_Output
PH0-OSC_IN.Mode=HSE-External-Oscillator
PH0-OSC_IN.Signal=RCC_OSC_IN
PH1-OSC_OUT.Mode=HSE-External-Oscillator
PH1-OSC_OUT.Signal=RCC_OSC_OUT
RCC.HSE_VALUE=8000000
RCC.SYSCLKFreq_VALUE=144000000
RCC.SYSCLKSource=RCC_SYSCLKSOURCE_PLLCLK
board=custom

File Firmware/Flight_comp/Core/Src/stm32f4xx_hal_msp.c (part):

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
    __HAL_RCC_GPIOA_CLK_ENABLE();
    /**ADC1 GPIO Configuration
    PA4     ------> ADC1_IN4
    */
    GPIO_InitStruct.Pin = BAT_VSENCE_Pin;
    GPIO_InitStruct.Mode = GPIO_MODE_ANALOG;
    GPIO_InitStruct.Pull = GPIO_NOPULL;
    HAL_GPIO_Init(BAT_VSENCE_GPIO_Port, &GPIO_InitStruct);

    /* USER CODE BEGIN ADC1_MspInit 1 */

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    __HAL_RCC_ADC1_CLK_DISABLE();

    /**ADC1 GPIO Configuration
    PA4     ------> ADC1_IN4
    */
    HAL_GPIO_DeInit(BAT_VSENCE_GPIO_Port, BAT_VSENCE_Pin);

    /* USER CODE BEGIN ADC1_MspDeInit 1 */

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
    __HAL_RCC_GPIOB_CLK_ENABLE();
    /**I2C1 GPIO Configuration
    PB6     ------> I2C1_SCL
    PB7     ------> I2C1_SDA
    */
    GPIO_InitStruct.Pin = EEP_SCL_Pin|EEP_SDA_Pin;
    GPIO_InitStruct.Mode = GPIO_MODE_AF_OD;
    GPIO_InitStruct.Pull = GPIO_PULLUP;
    GPIO_InitStruct.Speed = GPIO_SPEED_FREQ_VERY_HIGH;
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
    __HAL_RCC_GPIOB_CLK_ENABLE();
    /**I2C2 GPIO Configuration
    PB10     ------> I2C2_SCL
    PB11     ------> I2C2_SDA
    */
    GPIO_InitStruct.Pin = BMP_SCL_Pin|BMP_SDA_Pin;
    GPIO_InitStruct.Mode = GPIO_MODE_AF_OD;
    GPIO_InitStruct.Pull = GPIO_PULLUP;
    GPIO_InitStruct.Speed = GPIO_SPEED_FREQ_VERY_HIGH;
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    __HAL_RCC_GPIOC_CLK_ENABLE();
    __HAL_RCC_GPIOA_CLK_ENABLE();
    /**I2C3 GPIO Configuration
    PC9     ------> I2C3_SDA
    PA8     ------> I2C3_SCL
    */
    GPIO_InitStruct.Pin = GPS_SDA_Pin;
    GPIO_InitStruct.Mode = GPIO_MODE_AF_OD;
    GPIO_InitStruct.Pull = GPIO_PULLUP;
    GPIO_InitStruct.Speed = GPIO_SPEED_FREQ_VERY_HIGH;
    GPIO_InitStruct.Alternate = GPIO_AF4_I2C3;
    HAL_GPIO_Init(GPS_SDA_GPIO_Port, &GPIO_InitStruct);

    GPIO_InitStruct.Pin = GPS_SCL_Pin;
    GPIO_InitStruct.Mode = GPIO_MODE_AF_OD;
    GPIO_InitStruct.Pull = GPIO_PULLUP;
    GPIO_InitStruct.Speed = GPIO_SPEED_FREQ_VERY_HIGH;
    GPIO_InitStruct.Alternate = GPIO_AF4_I2C3;
    HAL_GPIO_Init(GPS_SCL_GPIO_Port, &GPIO_InitStruct);

    /* Peripheral clock enable */
    __HAL_RCC_I2C3_CLK_ENABLE();
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    __HAL_RCC_I2C1_CLK_DISABLE();

    /**I2C1 GPIO Configuration
    PB6     ------> I2C1_SCL
    PB7     ------> I2C1_SDA
    */
    HAL_GPIO_DeInit(EEP_SCL_GPIO_Port, EEP_SCL_Pin);

    HAL_GPIO_DeInit(EEP_SDA_GPIO_Port, EEP_SDA_Pin);

    /* USER CODE BEGIN I2C1_MspDeInit 1 */

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    __HAL_RCC_I2C2_CLK_DISABLE();

    /**I2C2 GPIO Configuration
    PB10     ------> I2C2_SCL
    PB11     ------> I2C2_SDA
    */
    HAL_GPIO_DeInit(BMP_SCL_GPIO_Port, BMP_SCL_Pin);

    HAL_GPIO_DeInit(BMP_SDA_GPIO_Port, BMP_SDA_Pin);

    /* USER CODE BEGIN I2C2_MspDeInit 1 */

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    __HAL_RCC_I2C3_CLK_DISABLE();

    /**I2C3 GPIO Configuration
    PC9     ------> I2C3_SDA
    PA8     ------> I2C3_SCL
    */
    HAL_GPIO_DeInit(GPS_SDA_GPIO_Port, GPS_SDA_Pin);

    HAL_GPIO_DeInit(GPS_SCL_GPIO_Port, GPS_SCL_Pin);

    /* USER CODE BEGIN I2C3_MspDeInit 1 */

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
    __HAL_RCC_GPIOA_CLK_ENABLE();
    /**SPI1 GPIO Configuration
    PA5     ------> SPI1_SCK
    PA6     ------> SPI1_MISO
    PA7     ------> SPI1_MOSI
    */
    GPIO_InitStruct.Pin = FLASH_SCK_Pin|FLASH_MISO_Pin|FLASH_MOSI_Pin;
    GPIO_InitStruct.Mode = GPIO_MODE_AF_PP;
    GPIO_InitStruct.Pull = GPIO_NOPULL;
    GPIO_InitStruct.Speed = GPIO_SPEED_FREQ_VERY_HIGH;
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
    __HAL_RCC_GPIOB_CLK_ENABLE();
    /**SPI2 GPIO Configuration
    PB12     ------> SPI2_NSS
    PB13     ------> SPI2_SCK
    PB14     ------> SPI2_MISO
    PB15     ------> SPI2_MOSI
    */
    GPIO_InitStruct.Pin = IMU_NSS_Pin|IMU_SCK_Pin|IMU_MISO_Pin|IMU_MOSI_Pin;
    GPIO_InitStruct.Mode = GPIO_MODE_AF_PP;
    GPIO_InitStruct.Pull = GPIO_NOPULL;
    GPIO_InitStruct.Speed = GPIO_SPEED_FREQ_VERY_HIGH;
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    __HAL_RCC_GPIOA_CLK_ENABLE();
    __HAL_RCC_GPIOC_CLK_ENABLE();
    /**SPI3 GPIO Configuration
    PA15     ------> SPI3_NSS
    PC10     ------> SPI3_SCK
    PC11     ------> SPI3_MISO
    PC12     ------> SPI3_MOSI
    */
    GPIO_InitStruct.Pin = LORA_NSS_Pin;
    GPIO_InitStruct.Mode = GPIO_MODE_AF_PP;
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    GPIO_InitStruct.Alternate = GPIO_AF6_SPI3;
    HAL_GPIO_Init(LORA_NSS_GPIO_Port, &GPIO_InitStruct);

    GPIO_InitStruct.Pin = LORA_SCK_Pin|LORA_MISO_Pin|LORA_MOSI_Pin;
    GPIO_InitStruct.Mode = GPIO_MODE_AF_PP;
    GPIO_InitStruct.Pull = GPIO_NOPULL;
    GPIO_InitStruct.Speed = GPIO_SPEED_FREQ_VERY_HIGH;
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    __HAL_RCC_SPI1_CLK_DISABLE();

    /**SPI1 GPIO Configuration
    PA5     ------> SPI1_SCK
    PA6     ------> SPI1_MISO
    PA7     ------> SPI1_MOSI
    */
    HAL_GPIO_DeInit(GPIOA, FLASH_SCK_Pin|FLASH_MISO_Pin|FLASH_MOSI_Pin);

    /* USER CODE BEGIN SPI1_MspDeInit 1 */

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    __HAL_RCC_SPI2_CLK_DISABLE();

    /**SPI2 GPIO Configuration
    PB12     ------> SPI2_NSS
    PB13     ------> SPI2_SCK
    PB14     ------> SPI2_MISO
    PB15     ------> SPI2_MOSI
    */
    HAL_GPIO_DeInit(GPIOB, IMU_NSS_Pin|IMU_SCK_Pin|IMU_MISO_Pin|IMU_MOSI_Pin);

    /* USER CODE BEGIN SPI2_MspDeInit 1 */

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    __HAL_RCC_SPI3_CLK_DISABLE();

    /**SPI3 GPIO Configuration
    PA15     ------> SPI3_NSS
    PC10     ------> SPI3_SCK
    PC11     ------> SPI3_MISO
    PC12     ------> SPI3_MOSI
    */
    HAL_GPIO_DeInit(LORA_NSS_GPIO_Port, LORA_NSS_Pin);

    HAL_GPIO_DeInit(GPIOC, LORA_SCK_Pin|LORA_MISO_Pin|LORA_MOSI_Pin);

    /* USER CODE BEGIN SPI3_MspDeInit 1 */

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    /* USER CODE END TIM3_MspPostInit 0 */
    __HAL_RCC_GPIOB_CLK_ENABLE();
    /**TIM3 GPIO Configuration
    PB4     ------> TIM3_CH1
    */
    GPIO_InitStruct.Pin = LED_Pin;
    GPIO_InitStruct.Mode = GPIO_MODE_AF_PP;
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
    __HAL_RCC_GPIOB_CLK_ENABLE();
    /**TIM4 GPIO Configuration
    PB8     ------> TIM4_CH3
    PB9     ------> TIM4_CH4
    */
    GPIO_InitStruct.Pin = SERVO5_Pin|SERVO6_Pin;
    GPIO_InitStruct.Mode = GPIO_MODE_AF_PP;
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
    __HAL_RCC_GPIOA_CLK_ENABLE();
    /**TIM5 GPIO Configuration
    PA0-WKUP     ------> TIM5_CH1
    PA1     ------> TIM5_CH2
    PA2     ------> TIM5_CH3
    PA3     ------> TIM5_CH4
    */
    GPIO_InitStruct.Pin = SERVO1_Pin|SERVO2_Pin|SERVO3_Pin|SERVO4_Pin;
    GPIO_InitStruct.Mode = GPIO_MODE_AF_PP;
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
    __HAL_RCC_GPIOA_CLK_ENABLE();
    /**USART1 GPIO Configuration
    PA9     ------> USART1_TX
    PA10     ------> USART1_RX
    */
    GPIO_InitStruct.Pin = GPS_TX_Pin|GPS_RX_Pin;
    GPIO_InitStruct.Mode = GPIO_MODE_AF_PP;
    GPIO_InitStruct.Pull = GPIO_NOPULL;
    GPIO_InitStruct.Speed = GPIO_SPEED_FREQ_VERY_HIGH;
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    __HAL_RCC_USART1_CLK_DISABLE();

    /**USART1 GPIO Configuration
    PA9     ------> USART1_TX
    PA10     ------> USART1_RX
    */
    HAL_GPIO_DeInit(GPIOA, GPS_TX_Pin|GPS_RX_Pin);

    /* USER CODE BEGIN USART1_MspDeInit 1 */

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
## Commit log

2025-12-02 First commit. stm32 pin setup
2025-12-08 jauni faili
2025-12-08 Deleted old files
2025-12-16 Forlder Hardware created
2025-12-21 Ignition system added
2025-12-23 pieliku IMU un vēl kaut ko
2025-12-23 vnk commitoju vēlreiz
2025-12-25 PCB added, minor changes
2025-12-29 PCB silkscreen, PCB dimensions
2025-12-30 Minor changes in silkscreen and power rails
2026-01-07 Kaut ko palaboju
2026-01-08 camera, impedance control
2026-01-08 final touches
2026-01-10 Production files
2026-01-10 Firmware template
2026-01-27 EEP, IMU, BMP drivers, .ds_store removed
2026-01-27 Servo driver
2026-01-27 GNSS driver
2026-01-27 LORA, CRC
2026-01-28 multiple build errors fixed
2026-01-29 Create docs folder

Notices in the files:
Firmware/Flight_comp/Core/Src/stm32f4xx_hal_msp.c:
Copyright (c) 2026 STMicroelectronics.
All rights reserved.
This software is licensed under terms that can be found in the LICENSE file
